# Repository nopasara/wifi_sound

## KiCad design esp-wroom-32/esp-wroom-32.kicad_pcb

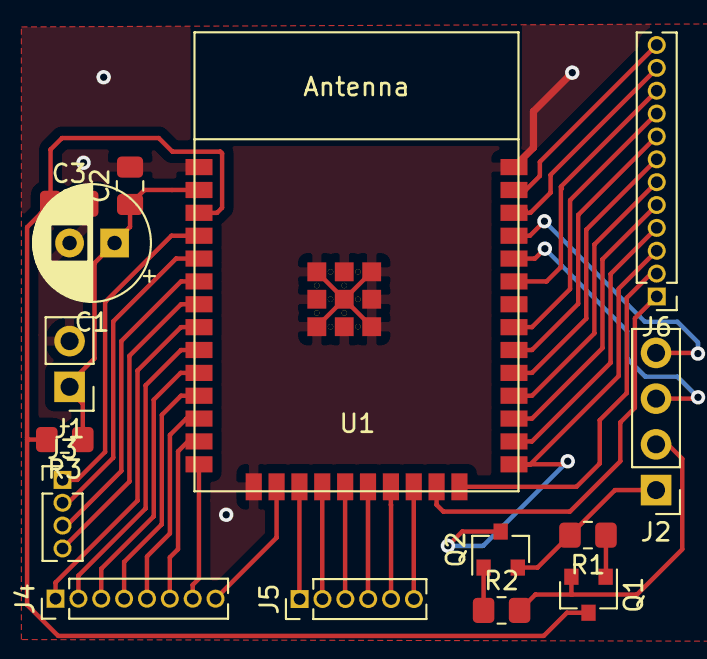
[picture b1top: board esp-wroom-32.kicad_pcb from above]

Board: 2 copper layers, 15 parts (0 on the bottom side), 39 nets.

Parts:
C1: 22uF; CP_Radial_D6.3mm_P2.50mm
C2, C3: 0.1uF; C_0805_2012Metric_Pad1.18x1.45mm_HandSolder
J1: Power; PinHeader_1x02_P2.54mm_Vertical
J2: USART; PinHeader_1x04_P2.54mm_Vertical
J3: Input; PinHeader_1x04_P1.27mm_Vertical
J4: Conn_01x08_Male; PinHeader_1x08_P1.27mm_Vertical
J5: Conn_01x06_Male; PinHeader_1x06_P1.27mm_Vertical
J6: Conn_01x12_Male; PinHeader_1x12_P1.27mm_Vertical
Q1, Q2: Q_NPN_BEC; SOT-23
R1, R2, R3: 10k; R_0805_2012Metric_Pad1.20x1.40mm_HandSolder
U1: esp-wroom-32

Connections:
3V3: C1.1, C2.1, J1.1, R3.1, U1.2
DTR: J2.1, Q2.2, R1.2
GND: C1.2, C2.2, C3.2, J1.2, U1.1, U1.15, U1.38, U1.39
unnamed: C3.1, Q1.3, R3.2, U1.3
unnamed: J3.1, U1.4
unnamed: J3.2, U1.5
unnamed: J3.3, U1.6
unnamed: J3.4, U1.7
unnamed: J4.1, U1.8
unnamed: J4.2, U1.9
unnamed: J4.3, U1.10
unnamed: J4.4, U1.11
unnamed: J4.5, U1.12
unnamed: J4.6, U1.13
unnamed: J4.7, U1.14
unnamed: J4.8, U1.16
unnamed: J5.1, U1.17
unnamed: J5.2, U1.18
unnamed: J5.3, U1.19
unnamed: J5.4, U1.20
unnamed: J5.5, U1.21
unnamed: J5.6, U1.22
unnamed: J6.1, U1.23
unnamed: J6.2, U1.24
unnamed: J6.3, Q2.3, U1.25
unnamed: J6.4, U1.26
unnamed: J6.5, U1.27
unnamed: J6.6, U1.28
unnamed: J6.7, U1.29
unnamed: J6.8, U1.30
unnamed: J6.9, U1.31
unnamed: J6.10, U1.33
unnamed: J6.11, U1.36
unnamed: J6.12, U1.37
unnamed: Q1.1, R1.1
unnamed: Q2.1, R2.1
RTS: J2.2, Q1.2, R2.2
RX: J2.4, U1.35
TX: J2.3, U1.34

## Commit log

2021-08-06 Initial wifi project commit
    KiCad project for the ESP-WROOM-32 test board supporting external
    CP2102 module for the module programming. Implements the DTS and RTS
    signals for auto flash mode selection
